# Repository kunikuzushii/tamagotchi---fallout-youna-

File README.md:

# Kaiser Pet 
tamagotchi project for fallout summer 2026
created by Youna Son (≧∇≦)ﾉ

ONSHAPE LINK:

https://cad.onshape.com/documents/d6c669abeeb3d7413e8d21f8/w/bde522f027b95c0c69872acb/e/c43f71f52c280984713279bd?renderMode=0&uiState=6a39e0cea890183796429e63

_________

# What is a Kaiser Pet? 

My custom themed tamagotchi has:
- RBG Screen
- Higher quality pixel art
- Photoresister (light sensor)

and most importantly... ITS FREAKING MICHAEL KAISER!!!

You take care of Kaiser from Blue Lock (animanga) like a standard tamagotchi. For example, you monitor their health, energy, and hunger levels and take care of them accordingly.

Hunger bar too low? 
Feed them!

Energy bar high?
Play with them!

Except it's better because you take care of the goat

______

# Why It Was Made? o((>ω< ))o

I cannot put into words for my love this character. The explanation behind it would likely take up 5 pages on a size 12, Times New Romans, single spaced google document for me to even START talking about it.
ps... you guys should see my embarassing pinterest page of over 300+ pins of Kaiser that made the zine process super easy (Sorry, I'm a pinterest warrior) AND my cosplays

Jokes aside, the main purpose is obviously: ENTERTAINMENT!

With the hype of the World Cup / FIFA, I think taking care of a character based off a soccer animanga would be super cool and fun.
Additionally, I really do want to use this regularly in my life, I love this character to the point where the whole event of fallout might've been an excuse to me building a super sick hardware project that suspiciously caters to my interests

# Pictures (☆▽☆)

CAD image:

Render images (in the zine):

PCB:

Sneak peek of my pixel art!:

______
## Bill of Materials

**Total Cost: $34.33**

| Name | Qty | Unit | Price (USD) | Total (USD) | MOQ | MOQ Price | Source |
| :--- | :---: | :---: | ---: | ---: | :---: | ---: | :--- |
| XIAO ESP32C3 | 1 | pcs | $4.99 | $4.99 | 1 | $4.99 | [Order](https://www.seeedstudio.com/Seeed-XIAO-ESP32C3-p-5431.html) |
| XHXDZ 1207-P6.5MM Buzzer | 1 | pcs | $0.50 | $5.03 | 10 | $5.03 | [Order](https://www.aliexpress.us/item/3256810135642750.html) |
| HS180S10B Screen | 1 | pcs | $3.21 | $3.21 | 1 | $3.21 | [Order](https://www.lcsc.com/product-detail/C5329585.html) |
| RC0805FR-0710KL Resistor | 1 | pcs | $0.10 | $0.10 | 1 | $0.10 | [Order](https://www.digikey.com/en/products/detail/yageo/RC0805FR-0710KL/727535) |
| GL12528 LDR | 1 | pcs | $0.31 | $1.56 | 5 | $1.56 | [Order](https://www.lcsc.com/product-detail/C559386.html) |
| M20-9990246 Connector | 1 | pcs | $0.10 | $0.10 | 1 | $0.10 | [Order](https://www.digikey.com/en/products/detail/harwin-inc/M20-9990246/3728226) |
| TSC016A04518A Tactile Switch | 3 | pcs | $0.01 | $0.54 | 50 | $0.54 | [Order](https://www.lcsc.com/product-detail/C2888493.html) |
| Battery | 1 | pcs | $6.20 | $6.20 | 1 | $6.20 | [Order](https://www.aliexpress.us/item/3256808658204287.html) |
| PCB | 1 | pcs | $0.40 | $2.00 | 5 | $2.00 | [Order](https://jlcpcb.com) |
| PLA Housing | 1 | pcs | - | - | - | - | Self-Print / Local |
| M3 x 10mm Socket Cap Head Screws | 3 | pcs | $0.47 | $1.88 | 4 | $1.88 | [Order](https://accu-components.com/us/metric-cap-head-screws/16004-SSCF-M3-10-12-9) |
| M3 x 5mm Socket Cap Head Screws | 5 | pcs | $0.31 | $1.86 | 6 | $1.86 | [Order](https://accu-components.com/us/metric-cap-head-screws/16001-SSCF-M3-5-12-9) |
| TS-107-T-AA Connector | 2 | pcs | $1.28 | $2.56 | 1 | $1.28 | [Order](https://www.digikey.com/en/products/detail/samtec-inc/TS-107-T-AA/10218878) |
| TS-110-T-A Connector | 2 | pcs | $ 2.15 | $4.30 | 1 | $2.15 | [Order](https://www.digikey.com/en/products/detail/samtec-inc/TS-110-T-A/1105484) |
Total Cost (USD) is the REAL price required before shipping fees
____

# BUILD & ASSEMBLY
___
# Required Tools
___
1) Solder
2) Sldering iron
3) Tweezers
4) 3D Printer
5) Screwdriver for M3 5mm & M3 10mm Screws
6) Electronic device to connect to tamagotchi through USB port

# Assembly Directions
____
1) Solder the Seeed Studio XIAO ESP32-C3, OLED display header connections, tact switches, battery connector, and all remaining through-hole and surface-mount components onto the PCB FOLLOWING the schematic/layout
2) Check for incomplete connections.
3) Press the buttons down until they fit. 
5) Route the battery leads to cable path and place the lipo battery into the battery compartment right below the pcb or just look under.
6) Solder/connect the battery to the PCB battery connector. Check for polarity!
7) Align PCB assembly with the mounting posts inside the bottom case and SLOWLY put it into place. 
8) Secure the PCB to the bottom case using 3× M3 mounting screws, tightening them evenly. Please focus on tightening them properly before it just falls out. (haha, falls out like. fallout. haha)
9) Verify that it aligns again. This is super important!
10) Position the top case onto the bottom case.
11) Fasten the enclosure halves together using the specified M1.6 screws, tightening each screw gradually in an alternating pattern to ensure even clamping.
12) Install all the software libraries in Arduino.
13) Connect the XIAO ESP32-C3 to a computer using a USB-C cable and select the correct board and COM port within the Arduino IDE.
14) Compile firmware! Check everything including error messages (shouldn't be any).
bonus - since my sprites are in a separate file due to the upgraded OLED, you can easily change up the sprites to whatever you want as long as you edit the kaiser_sprites.h properly
15) Upload the firmware to the ESP32-C3, make sure you get the completion message.
16) Turn it on or off to check if it connects properly especially without USB connection.
17) Test the OLED if it renders my beautiful pixel art properly + status bar. 
18) Test all button inputs, you can manipulate the button functions off the firmware if you really want to.
19) Confirm everything else: charging, functioning, missing pixels, etc.

Congrats! I hope someone can actually enjoy this and build it for themselves!

# CREDITS:
- ONSHAPE (for CAD)
- KiCAD (all hardware / PCB stuff)
- Fallout

LIBRARIES CREDITS
## Dependencies
You need these libraries (add to Arduino libraries managers)
* **Adafruit GFX Library** (by Adafruit)
* **Adafruit ST7735 and ST7789 Library** (by Adafruit)
* **SPI** (Built-in to Arduino IDE)

# PIXEL ART AND ZINE CREDITS
REFERENCES AND INSPIRATION (Pinterest!) :

- https://www.pinterest.com/pin/168322104817334436/
- https://www.pinterest.com/pin/888123989041302114/
- https://www.pinterest.com/pin/114560384269168373/
- https://www.pinterest.com/pin/888123989035366728/
- https://www.pinterest.com/pin/888123989035906915/
- https://pin.it/148EMhVAn
- https://share.google/kxDoDrVdniUi0Naia
- https://pin.it/6CnxexgHx

and obviously, kudos to Muneyuki Kaneshiro for making my favorite character and Yusuke Nomura for bringing him to life by drawing him.

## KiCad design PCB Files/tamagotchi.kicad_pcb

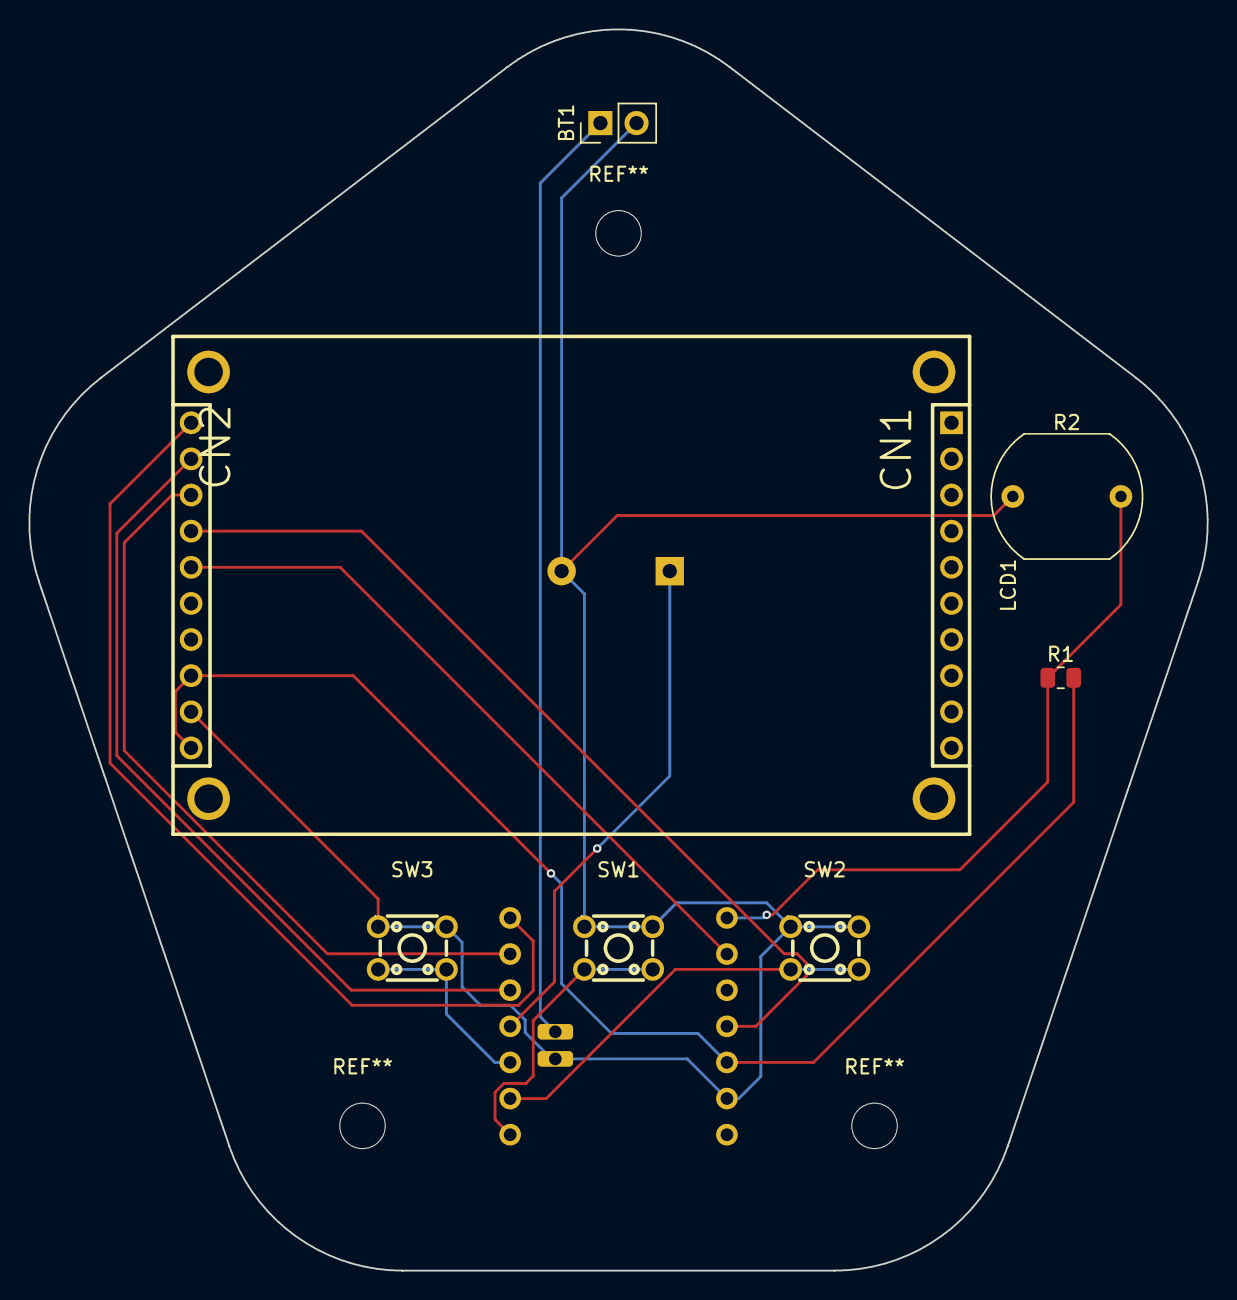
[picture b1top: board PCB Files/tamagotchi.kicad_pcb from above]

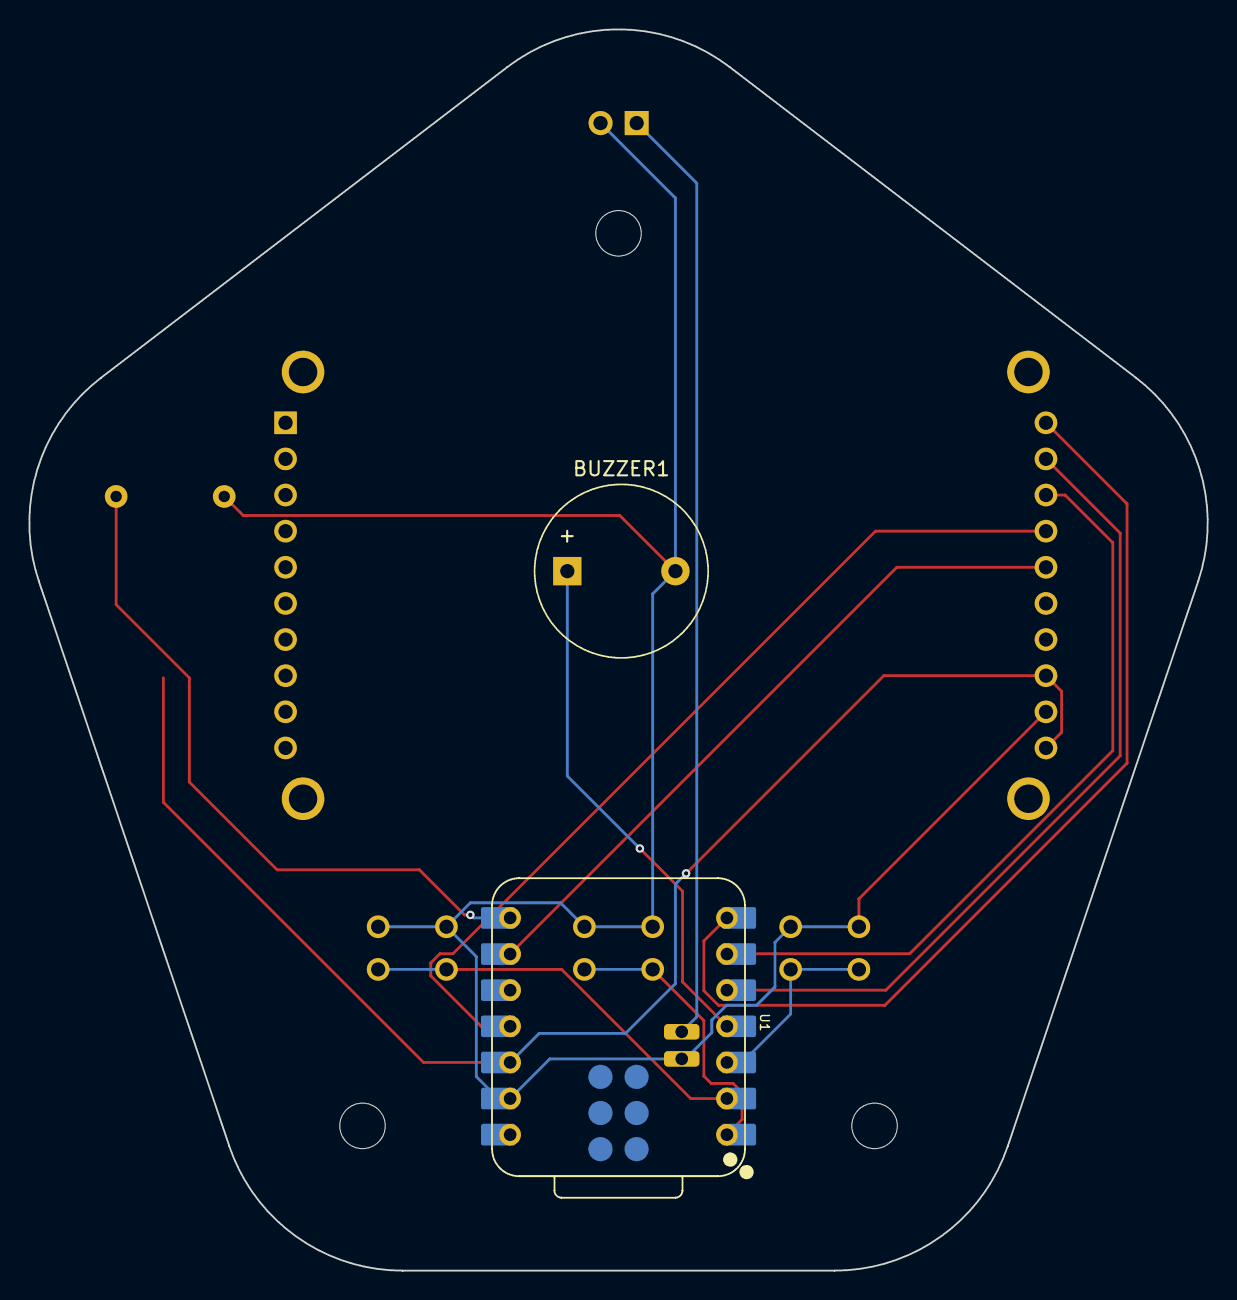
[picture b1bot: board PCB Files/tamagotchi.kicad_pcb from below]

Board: 2 copper layers, 82.8 x 87.3 mm, 9 parts (2 on the bottom side), 13 nets.

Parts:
BT1: Battery_Cell; PinHeader_1x02_P2.54mm_Vertical
BUZZER1: 1207-P6.5MM; Buzzer_12x9.5RM7.6
LCD1: HS180S10B; LCD-TH_L56.0-W35.0-P2.54_HS180S10B
R1: 10k; R_0805_2012Metric
R2: LDR03; R_LDR_10x8.5mm_P7.6mm_Vertical
SW1, SW2, SW3: SW_Push; SW-TH_4P-L4.5-W4.5-P3.00-LS4.8
U1: XIAO-ESP32-C3-SMD; XIAO-ESP32-C3-DIP-SMD

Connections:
+3V3: LCD1.11, LCD1.13, R1.2, U1.12 (3V3)
+BATT: BT1.1 (+), U1.15
/CS1: LCD1.20, U1.7 (GPIO21_D6_TX)
/DC: LCD1.18, U1.6 (GPIO7_D5_SCL)
/RES: LCD1.19, U1.5 (GPIO6_D4_SDA)
GND: BT1.2 (-), BUZZER1.2 (-), LCD1.12, R2.1, SW1.1, SW2.1, SW3.1, U1.13 (GND), U1.16
unnamed: BUZZER1.1 (+), U1.4 (GPIO5_A3_D3)
unnamed: SW1.2, U1.1 (GPIO2_A0_D0)
unnamed: SW2.2, U1.2 (GPIO3_A1_D1)
unnamed: SW3.2, U1.3 (GPIO4_A2_D2)
unnamed: LCD1.16, U1.9 (GPIO8_D8_SCK)
unnamed: LCD1.17, U1.11 (GPIO10_D10_MOSI)
unnamed: R1.1, R2.2, U1.8 (GPIO20_D7_RX)

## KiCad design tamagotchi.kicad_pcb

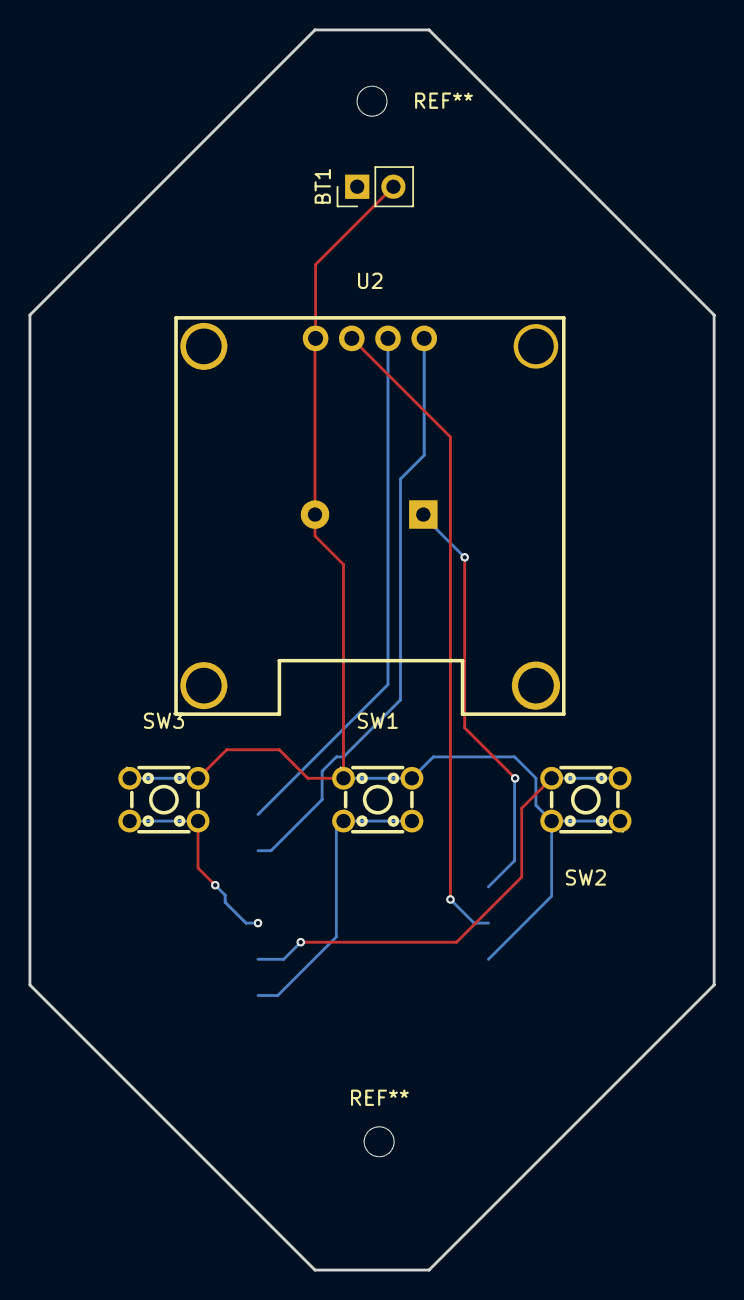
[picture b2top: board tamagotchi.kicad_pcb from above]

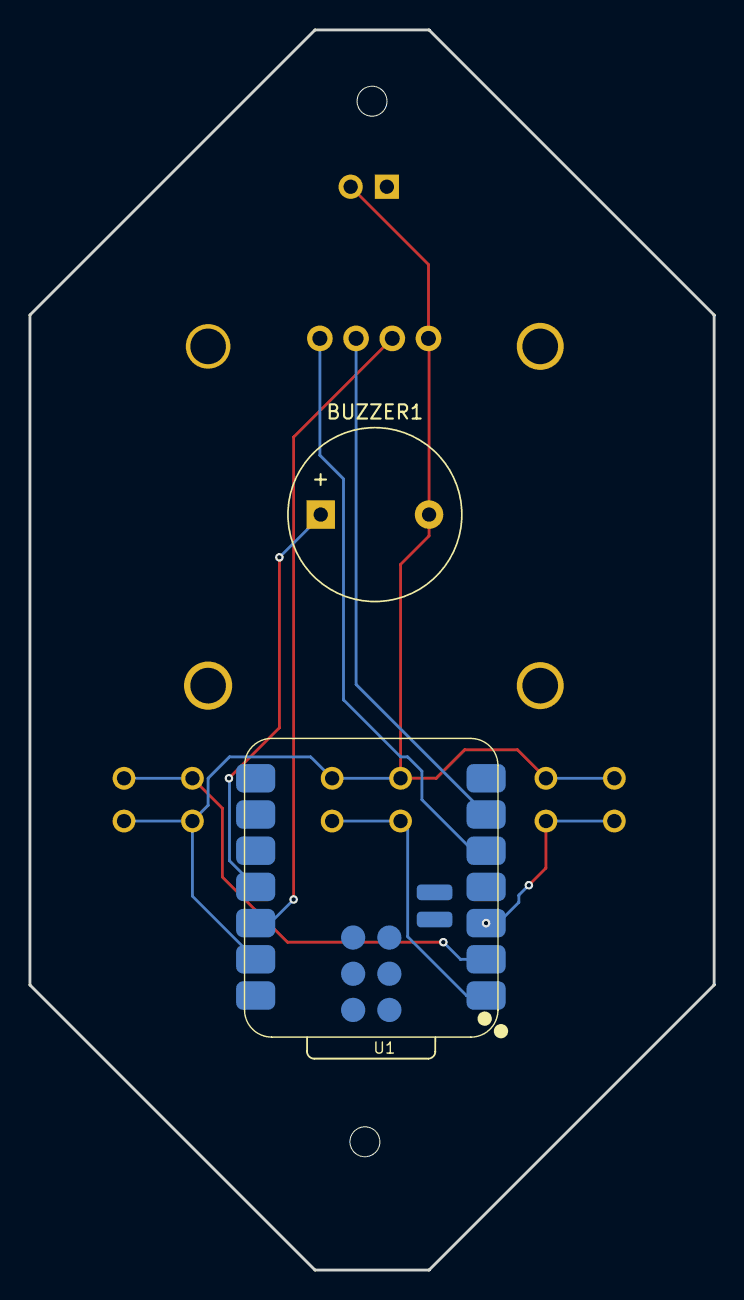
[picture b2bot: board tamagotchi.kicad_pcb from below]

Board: 2 copper layers, 48.0 x 87.0 mm, 7 parts (2 on the bottom side), 8 nets.

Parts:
BT1: Battery_Cell; PinHeader_1x02_P2.54mm_Vertical
BUZZER1: 1207-P6.5MM; Buzzer_12x9.5RM7.6
SW1, SW2, SW3: SW_Push; SW-TH_4P-L4.5-W4.5-P3.00-LS4.8
U1: XIAO-ESP32-C3-SMD
U2: HS96L03W2C03; OLED-TH_L27.8-W27.2-P2.54_C9900033791

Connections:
+3V3: U1.12 (3V3), U2.2 (VCC)
GND: BT1.2 (-), BUZZER1.2 (-), SW1.1, SW2.1, SW3.1, U1.13 (GND), U2.1 (GND)
unnamed: BUZZER1.1 (+), U1.11 (GPIO10_D10_MOSI)
unnamed: SW1.2, U1.1 (GPIO2_A0_D0)
unnamed: SW2.2, U1.2 (GPIO3_A1_D1)
unnamed: SW3.2, U1.3 (GPIO4_A2_D2)
unnamed: U1.5 (GPIO6_D4_SDA), U2.4 (SDA)
unnamed: U1.6 (GPIO7_D5_SCL), U2.3 (SCL)

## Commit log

2026-06-21 Add BOM.csv with bill of materials details
2026-06-21 Create hi
2026-06-21 Add components and pricing to BOM CSV
2026-06-21 Create mkl
2026-06-21 Create bleh
2026-06-21 i thought i added the pdf idk
2026-06-21 Rename download to .step
2026-06-22 Create wia
2026-06-23 changed grammar issues and added fun and engaging language
2026-06-25 name change the zine pdf
2026-06-25 file name change
2026-06-27 name change
2026-06-27 Revise README with project updates and assembly details
    Updated project details, added images, and revised assembly instructions.
